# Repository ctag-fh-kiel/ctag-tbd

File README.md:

# dadamachines TBD-16

The first standalone desktop audio DSP platform based on [CTAG TBD](https://github.com/ctag-fh-kiel/ctag-tbd), with standard MIDI connectivity — designed to bring open-source audio processing beyond Eurorack.

**TBD-16** combines 50+ high-quality generators and effects in a modular, extensible architecture. It is built for musicians, educators, and audio researchers who want hands-on DSP without proprietary lock-in.

## Documentation

**[dadamachines.github.io/ctag-tbd](https://dadamachines.github.io/ctag-tbd/)**

## What This Fork Does

This repository is a fork of [ctag-fh-kiel/ctag-tbd](https://github.com/ctag-fh-kiel/ctag-tbd) (branch `p4_main`), adapted for the **dadamachines TBD-16** hardware. Our focus:

- **UI/UX** — Redesigned web interface with musician-friendly interaction patterns
- **Documentation** — Clear guides, example workflows, and UX guidelines for plugin developers
- **Desktop Hardware** — Standalone form factor with standard MIDI, no Eurorack required

The DSP engine, plugin system, and core firmware are developed upstream by [Robert Manzke / CTAG](https://www.creative-technologies.de/).

## Getting Started

See the [documentation](https://dadamachines.github.io/ctag-tbd/) for setup guides, plugin reference, and flashing instructions.

## Hardware Configurations

The firmware supports four hardware configurations for different board
variants — from a minimal flash-only build to the full TBD-16 with SD card
and RP2350 sequencer bridge. See [HARDWARE_CONFIGURATIONS.md](HARDWARE_CONFIGURATIONS.md) for
the feature matrix, build instructions, and Kconfig flag reference.

## Project Structure

```
components/         DSP plugins and sound processors
docs/               Sphinx documentation source
main/               Firmware entry point and system management
sdcard_image/       SD card image (samples, kits, presets, web UI)
simulator/          Desktop simulator for plugin development
tools/              Build scripts and sample utilities
generators/         Plugin scaffolding templates
```

### Building Documentation Locally

To build and preview the documentation (including the blog) on your local machine:

1.  **Install requirements**:
    ```bash
    pip install -r docs/requirements.txt
    ```

2.  **Build HTML**:
    ```bash
    sphinx-build -b html -c docs/config docs build/docs
    ```
    
3.  **View**:
    Open `build/docs/index.html` in your browser.

## Community & Support

- [dadamachines Forum](https://forum.dadamachines.com) -- Ask questions, share patches, and connect with other TBD users and developers.
- [GitHub Issues](https://github.com/dadamachines/ctag-tbd/issues) -- Bug reports and feature requests.

## Contributing

Contributions are welcome — see [CONTRIBUTING.md](CONTRIBUTING.md) for the
full guide covering the branch model, CI pipelines, build instructions,
and artifact naming conventions.

## Acknowledgements

**CTAG TBD** was created by [Robert Manzke](https://github.com/ctag-fh-kiel/ctag-tbd) at the [Creative Technologies Arbeitsgruppe](https://www.creative-technologies.de/), Kiel University of Applied Sciences. 

The TBD-16 adaptation is led by [dadamachines](https://dadamachines.com).

UX and instrument design contributions by [Benjamin Weiss / instrument-design](https://instrument-design.com/work/).

## Funding

This project is partially funded through the [NGI0 Commons Fund](https://nlnet.nl/commonsfund), established by [NLnet](https://nlnet.nl/) with financial support from the European Commission's [Next Generation Internet](https://ngi.eu/) programme, under grant agreement No [101135429](https://cordis.europa.eu/project/id/101135429).

Not all work on TBD / TBD-16 is covered by NLnet funding.

## License

This repository contains code under two open-source software licenses:

**Core DSP Engine** (upstream [ctag-fh-kiel/ctag-tbd](https://github.com/ctag-fh-kiel/ctag-tbd)) -- [GNU General Public License (GPL 3.0)](https://www.gnu.org/licenses/gpl-3.0.txt). The audio engine, sound processors, and platform core. Modifications must be released under the same terms.

**dadamachines Additions** (web UI, browser-based flasher, plugins, documentation, tools) -- [GNU Lesser General Public License (LGPL 3.0)](https://www.gnu.org/licenses/lgpl-3.0.txt). Individual developers can freely use and contribute without copyleft affecting their own unrelated code. Companies must share modifications back or obtain a [commercial license](https://dadamachines.com/contact/).

**TBD-Core & TBD-16 Hardware** -- The dadamachines TBD-16 (desktop instrument) and TBD-Core (core DSP board for custom products) hardware designs are proprietary.

**Planned Open-Hardware Core Design** -- An open-hardware core design based on the same ESP32-P4 + RP2350 platform is planned for future publication in KiCad as an open-source reference.

**Original CTAG Hardware** (V1/V2) -- [Creative Commons Attribution-NonCommercial-ShareAlike 4.0 International (CC BY-NC-SA 4.0)](https://creativecommons.org/licenses/by-nc-sa/4.0/).

Copyright (c) 2020-2026 Robert Manzke. All rights reserved. (CTAG TBD core)

Copyright (c) 2014-2026 Johannes Elias Lohbihler for dadamachines. (TBD-16 adaptation, UI/UX, and Documentation)

See [LICENSE](LICENSE) for full details including trademark and commercial use terms.

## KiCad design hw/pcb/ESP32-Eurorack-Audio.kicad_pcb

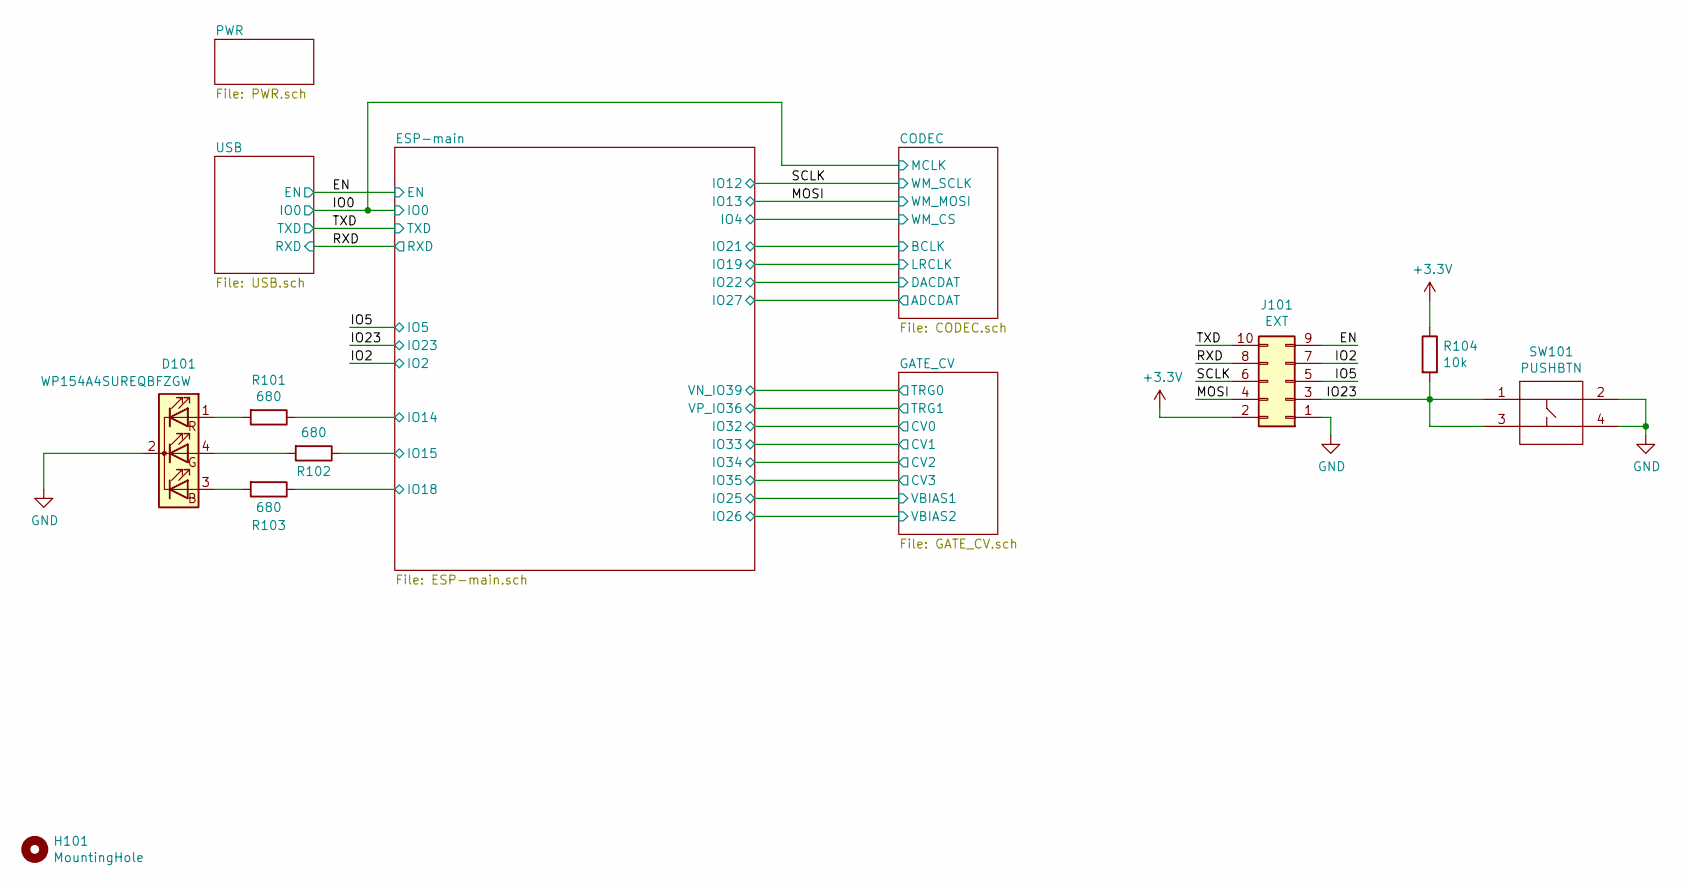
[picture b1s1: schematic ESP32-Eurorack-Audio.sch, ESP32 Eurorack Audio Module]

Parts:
D101: WP154A4SUREQBFZGW; LED_D5.0mm-4_RGB_Staggered_Pins
H101: MountingHole; MountingHole_2.7mm_M2.5_ISO7380
J101: EXT; PinHeader_2x05_P2.54mm_Vertical_SMD
R101, R102, R103: 680; R_0402_1005Metric
R104: 10k; R_0402_1005Metric
SW101: PUSHBTN; TactilePB_6x6

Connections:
+3V3: J101.2, R104.1; also elsewhere on the board
/EN: J101.9; also elsewhere on the board
/ESP-main/IO14: R101.1; also elsewhere on the board
/ESP-main/IO15: R102.1; also elsewhere on the board
/ESP-main/IO18: R103.1; also elsewhere on the board
/IO2: J101.7; also elsewhere on the board
/IO5: J101.5; also elsewhere on the board
/IO23: J101.3, R104.2, SW101.1, SW101.3; also elsewhere on the board
/MOSI: J101.4; also elsewhere on the board
/RXD: J101.8; also elsewhere on the board
/SCLK: J101.6; also elsewhere on the board
/TXD: J101.10; also elsewhere on the board
GND: D101.2 (K), J101.1, SW101.2, SW101.4; also elsewhere on the board
unnamed: D101.1 (RA), R101.2
unnamed: D101.3 (BA), R103.2
unnamed: D101.4 (GA), R102.2

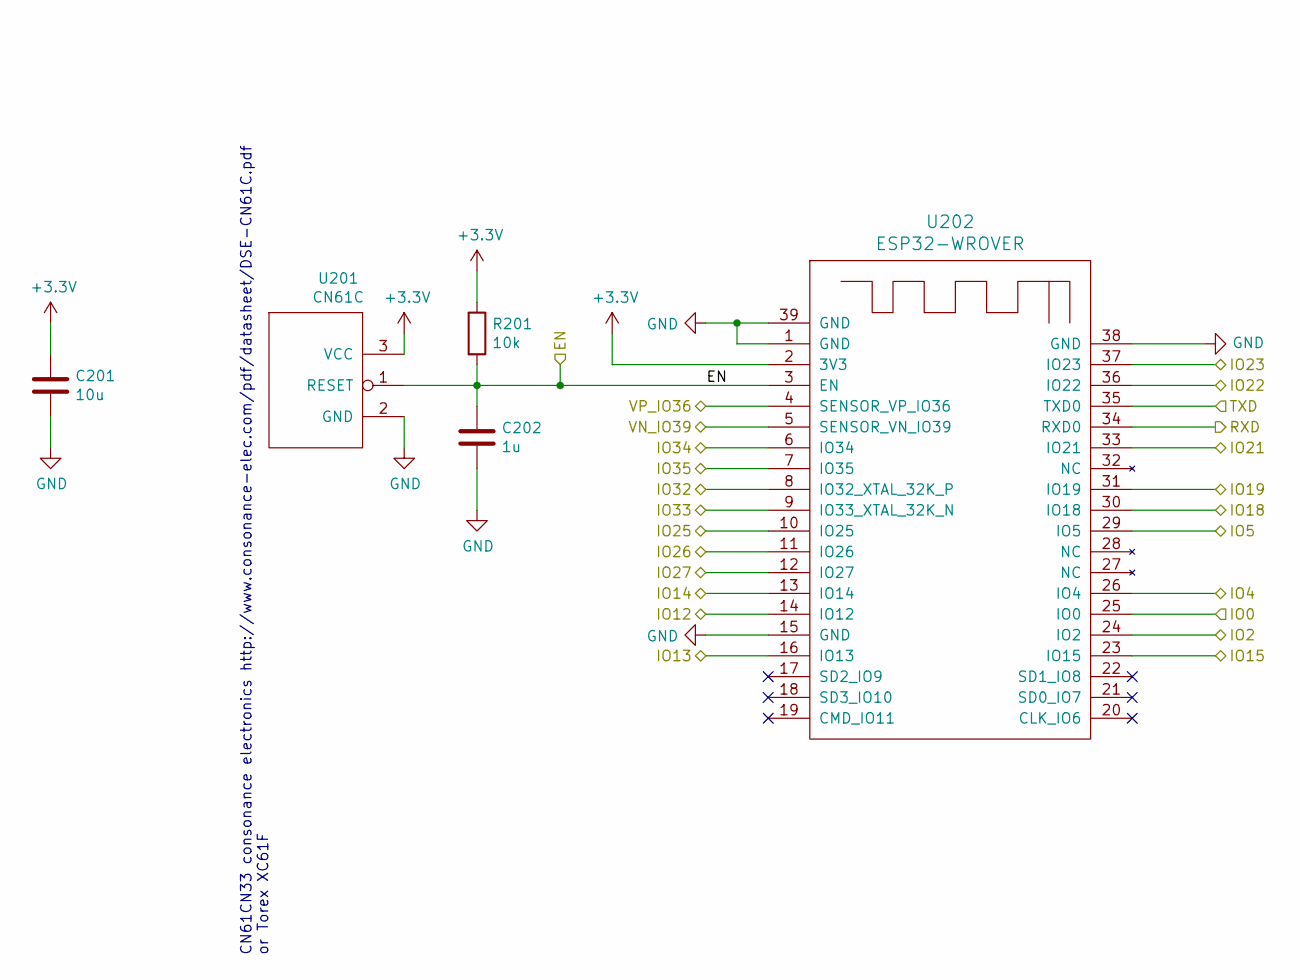
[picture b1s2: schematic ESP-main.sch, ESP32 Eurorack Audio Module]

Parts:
C201: 10u; C_0402_1005Metric
C202: 1u; C_0402_1005Metric
R201: 10k; R_0402_1005Metric
U201: CN61C; SOT-23
U202: ESP32-WROVER

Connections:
+3V3: C201.1, R201.1, U201.3 (VCC), U202.2 (3V3); also elsewhere on the board
/CODEC/ADCDAT: U202.12 (IO27); also elsewhere on the board
/CODEC/BCLK: U202.33 (IO21); also elsewhere on the board
/CODEC/DACDAT: U202.36 (IO22); also elsewhere on the board
/EN: C202.1, R201.2, U201.1 (RESET), U202.3 (EN); also elsewhere on the board
/ESP-main/IO4: U202.26 (IO4); also elsewhere on the board
/ESP-main/IO14: U202.13 (IO14); also elsewhere on the board
/ESP-main/IO15: U202.23 (IO15); also elsewhere on the board
/ESP-main/IO18: U202.30 (IO18); also elsewhere on the board
/ESP-main/IO19: U202.31 (IO19); also elsewhere on the board
/ESP-main/IO25: U202.10 (IO25); also elsewhere on the board
/ESP-main/IO26: U202.11 (IO26); also elsewhere on the board
/GATE_CV/CV0: U202.8 (IO32_XTAL_32K_P); also elsewhere on the board
/GATE_CV/CV1: U202.9 (IO33_XTAL_32K_N); also elsewhere on the board
/GATE_CV/CV2: U202.6 (IO34); also elsewhere on the board
/GATE_CV/CV3: U202.7 (IO35); also elsewhere on the board
/GATE_CV/TRG0: U202.5 (SENSOR_VN_IO39); also elsewhere on the board
/GATE_CV/TRG1: U202.4 (SENSOR_VP_IO36); also elsewhere on the board
/IO0: U202.25 (IO0); also elsewhere on the board
/IO2: U202.24 (IO2); also elsewhere on the board
/IO5: U202.29 (IO5); also elsewhere on the board
/IO23: U202.37 (IO23); also elsewhere on the board
/MOSI: U202.16 (IO13); also elsewhere on the board
/RXD: U202.34 (RXD0); also elsewhere on the board
/SCLK: U202.14 (IO12); also elsewhere on the board
/TXD: U202.35 (TXD0); also elsewhere on the board
GND: C201.2, C202.2, U201.2 (GND), U202.1 (GND), U202.15 (GND), U202.38 (GND), U202.39 (GND); also elsewhere on the board

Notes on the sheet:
CN61CN33 consonance electronics http://www.consonance-elec.com/pdf/datasheet/DSE-CN61C.pdf or Torex XC61F

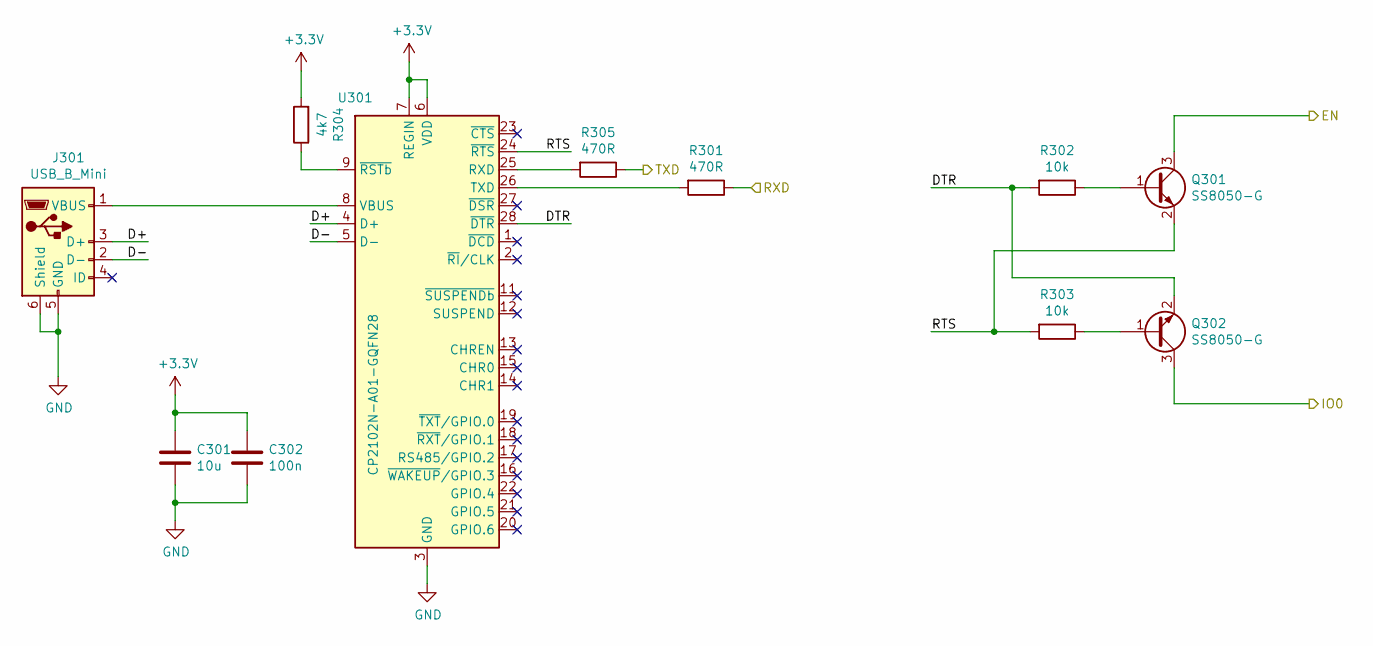
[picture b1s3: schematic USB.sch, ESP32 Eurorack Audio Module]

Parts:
C301: 10u; C_0402_1005Metric
C302: 100n; C_0402_1005Metric
J301: USB_B_Mini; USB_Mini-B_Tensility_54-00023_Vertical
Q301, Q302: SS8050-G; SOT-23
R301, R305: 470R; R_0402_1005Metric
R302, R303: 10k; R_0402_1005Metric
R304: 4k7; R_0402_1005Metric
U301: CP2102N-A01-GQFN28; QFN-28-1EP_5x5mm_P0.5mm_EP3.35x3.35mm

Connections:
+3V3: C301.1, C302.1, R304.2, U301.6 (VDD), U301.7 (REGIN); also elsewhere on the board
/EN: Q301.3 (C); also elsewhere on the board
/IO0: Q302.3 (C); also elsewhere on the board
/RXD: R301.1; also elsewhere on the board
/TXD: R305.1; also elsewhere on the board
/USB/D+: J301.3 (D+), U301.4 (D+)
/USB/D-: J301.2 (D-), U301.5 (D-)
/USB/DTR: Q302.2 (E), R302.2, U301.28 (~DTR)
/USB/RTS: Q301.2 (E), R303.2, U301.24 (~RTS)
GND: C301.2, C302.2, J301.5 (GND), J301.6 (Shield), U301.3 (GND), U301.29 (GND); also elsewhere on the board
unnamed: J301.1 (VBUS), U301.8 (VBUS)
unnamed: Q301.1 (B), R302.1
unnamed: Q302.1 (B), R303.1
unnamed: R301.2, U301.26 (TXD)
unnamed: R304.1, U301.9 (~RSTb)
unnamed: R305.2, U301.25 (RXD)

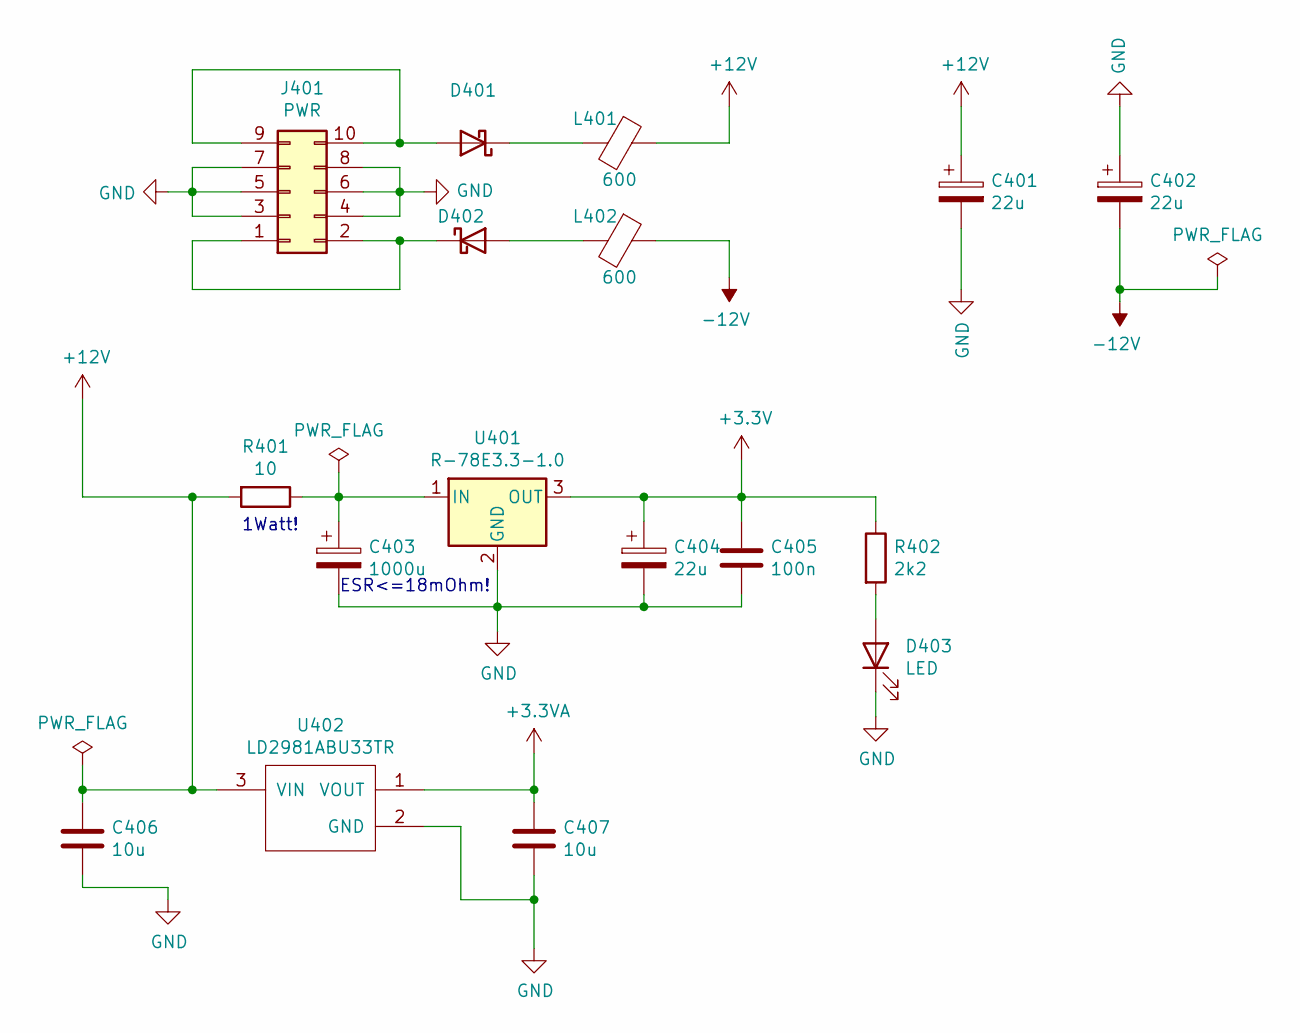
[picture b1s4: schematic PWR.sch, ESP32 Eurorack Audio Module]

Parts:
C401, C402, C404: 22u; C_0805_2012Metric
C403: 1000u; CP_Elec_10x12.6
C405: 100n; C_0402_1005Metric
C406: 10u; C_0805_2012Metric
C407: 10u; C_0402_1005Metric
D401, D402: D_SOD-123
D403: LED; LED_0805_2012Metric
J401: PWR; PinHeader_2x05_P2.54mm_Vertical
L401, L402: 600; C_0805_2012Metric
R401: 10; R_2512_6332Metric
R402: 2k2; R_0402_1005Metric
U401: R-78E3.3-1.0; SIP3_11.6x8.5mm
U402: LD2981ABU33TR; SOT-89-3

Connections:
+3.3VA: C407.1, U402.1 (VOUT); also elsewhere on the board
+3V3: C404.1, C405.1, R402.1, U401.3 (OUT); also elsewhere on the board
+12V: C401.1, C406.1, L401.1, R401.2, U402.3 (VIN); also elsewhere on the board
-12V: C402.2, L402.1; also elsewhere on the board
GND: C401.2, C402.1, C403.2, C404.2, C405.2, C406.2, C407.2, D403.1 (K), J401.3, J401.4, J401.5, J401.6, J401.7, J401.8, U401.2 (GND), U402.2 (GND); also elsewhere on the board
unnamed: C403.1, R401.1, U401.1 (IN)
unnamed: D401.1 (K), L401.2
unnamed: D401.2 (A), J401.9, J401.10
unnamed: D402.1 (K), J401.1, J401.2
unnamed: D402.2 (A), L402.2
unnamed: D403.2 (A), R402.2

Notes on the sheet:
ESR<=18mOhm!
1Watt!

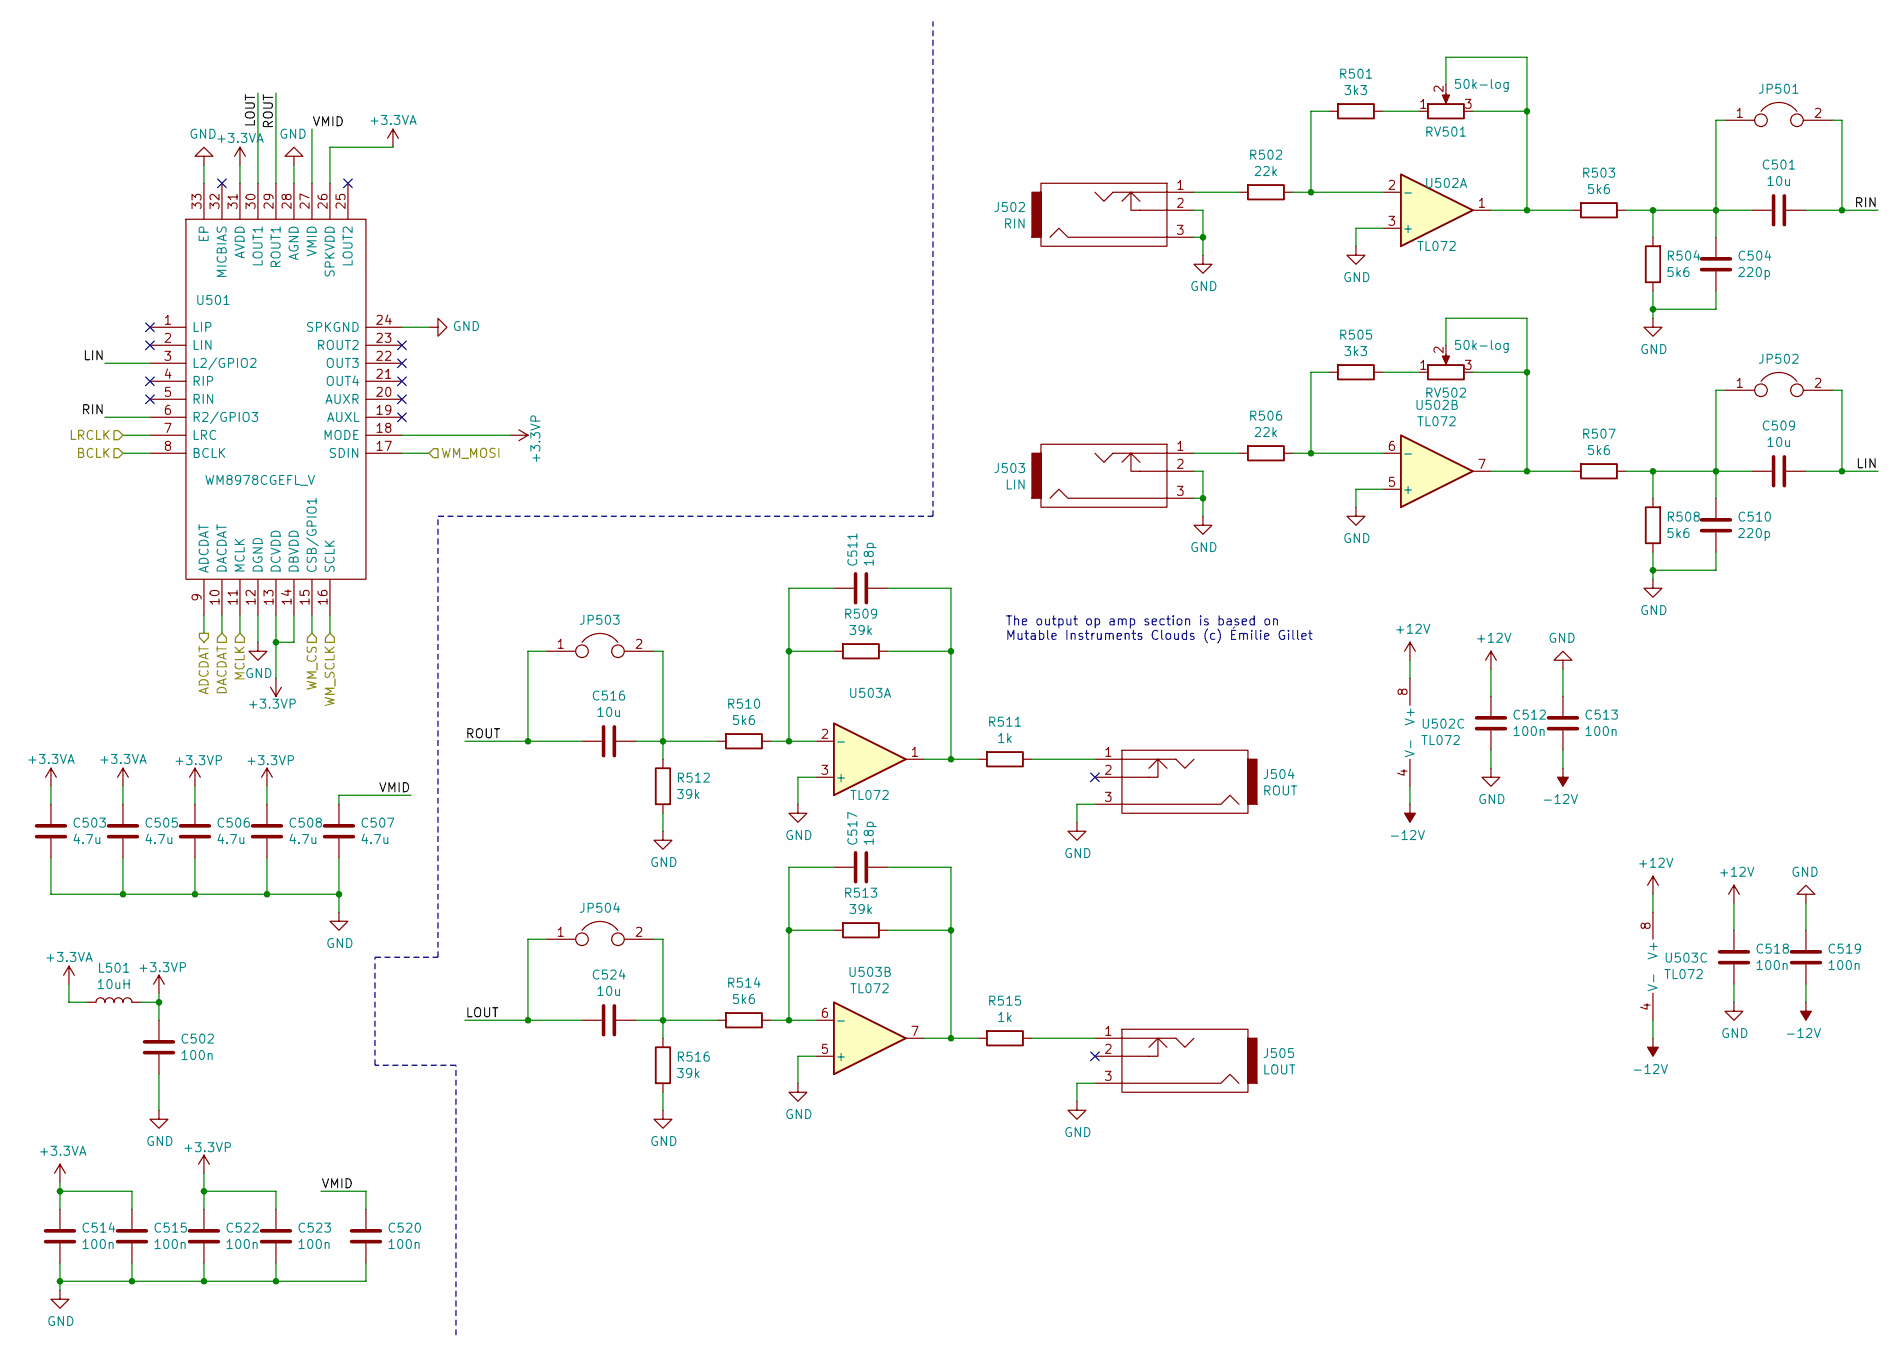
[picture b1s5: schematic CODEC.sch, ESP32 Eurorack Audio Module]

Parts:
C501, C509, C516, C524: 10u; C_0402_1005Metric
C502, C512, C513, C514, C515, C518, C519, C520, C522, C523: 100n; C_0402_1005Metric
C503, C505, C506, C507, C508: 4.7u; C_0402_1005Metric
C504, C510: 220p; C_0402_1005Metric
C511, C517: 18p; C_0402_1005Metric
J502: RIN; THONKICONN
J503: LIN; THONKICONN
J504: ROUT; THONKICONN
J505: LOUT; THONKICONN
JP501, JP502, JP503, JP504: SolderJumper-2_P1.3mm_Open_RoundedPad1.0x1.5mm
L501: 10uH; C_0603_1608Metric
R501, R505: 3k3; R_0402_1005Metric
R502, R506: 22k; R_0402_1005Metric
R503, R504, R507, R508, R510, R514: 5k6; R_0402_1005Metric
R509, R512, R513, R516: 39k; R_0402_1005Metric
R511, R515: 1k; R_0402_1005Metric
RV501, RV502: 50k-log; THONK-SONG-HUEI-R0904N-L-25-KQ_RED
U501: WM8978CGEFL_V; QFN-32-1EP_5x5mm_P0.5mm_EP3.65x3.65mm_ThermalVias; Mouser Part Number 238-WM8978CGEFL/V
U502, U503: TL072; SOIC-8_3.9x4.9mm_P1.27mm

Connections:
+3.3VA: C503.1, C505.1, C514.1, C515.1, L501.1, U501.26 (SPKVDD), U501.31 (AVDD); also elsewhere on the board
+3.3VP: C502.1, C506.1, C508.1, C522.1, C523.1, L501.2, U501.13 (DCVDD), U501.14 (DBVDD), U501.18 (MODE)
+12V: C512.1, C518.1, U502.8 (V+), U503.8 (V+); also elsewhere on the board
-12V: C513.2, C519.2, U502.4 (V-), U503.4 (V-); also elsewhere on the board
/CODEC/ADCDAT: U501.9 (ADCDAT); also elsewhere on the board
/CODEC/BCLK: U501.8 (BCLK); also elsewhere on the board
/CODEC/DACDAT: U501.10 (DACDAT); also elsewhere on the board
/CODEC/LIN: C509.1, JP502.2, U501.3 (L2/GPIO2)
/CODEC/LOUT: C524.2, JP504.1, U501.30 (LOUT1)
/CODEC/RIN: C501.1, JP501.2, U501.6 (R2/GPIO3)
/CODEC/ROUT: C516.2, JP503.1, U501.29 (ROUT1)
/CODEC/VMID: C507.1, C520.1, U501.27 (VMID)
/ESP-main/IO4: U501.15 (CSB/GPIO1); also elsewhere on the board
/ESP-main/IO19: U501.7 (LRC); also elsewhere on the board
/IO0: U501.11 (MCLK); also elsewhere on the board
/MOSI: U501.17 (SDIN); also elsewhere on the board
/SCLK: U501.16 (SCLK); also elsewhere on the board
GND: C502.2, C503.2, C504.2, C505.2, C506.2, C507.2, C508.2, C510.2, C512.2, C513.1, C514.2, C515.2, C518.2, C519.1, C520.2, C522.2, C523.2, J502.2, J502.3, J503.2, J503.3, J504.3, J505.3, R504.1, R508.1, R512.2, R516.2, U501.12 (DGND), U501.24 (SPKGND), U501.28 (AGND), U501.33 (EP), U502.3 (+), U502.5 (+), U503.3 (+), U503.5 (+); also elsewhere on the board
unnamed: C501.2, C504.1, JP501.1, R503.1, R504.2
unnamed: C509.2, C510.1, JP502.1, R507.1, R508.2
unnamed: C511.1, R509.2, R510.1, U503.2 (-)
unnamed: C511.2, R509.1, R511.2, U503.1
unnamed: C516.1, JP503.2, R510.2, R512.1
unnamed: C517.1, R513.2, R514.1, U503.6 (-)
unnamed: C517.2, R513.1, R515.2, U503.7
unnamed: C524.1, JP504.2, R514.2, R516.1
unnamed: J502.1, R502.2
unnamed: J503.1, R506.2
unnamed: J504.1, R511.1
unnamed: J505.1, R515.1
unnamed: R501.1, RV501.1
unnamed: R501.2, R502.1, U502.2 (-)
unnamed: R503.2, RV501.2, RV501.3, U502.1
unnamed: R505.1, RV502.1
unnamed: R505.2, R506.1, U502.6 (-)
unnamed: R507.2, RV502.2, RV502.3, U502.7

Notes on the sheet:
The output op amp section is based on Mutable Instruments Clouds (c) Émilie Gillet

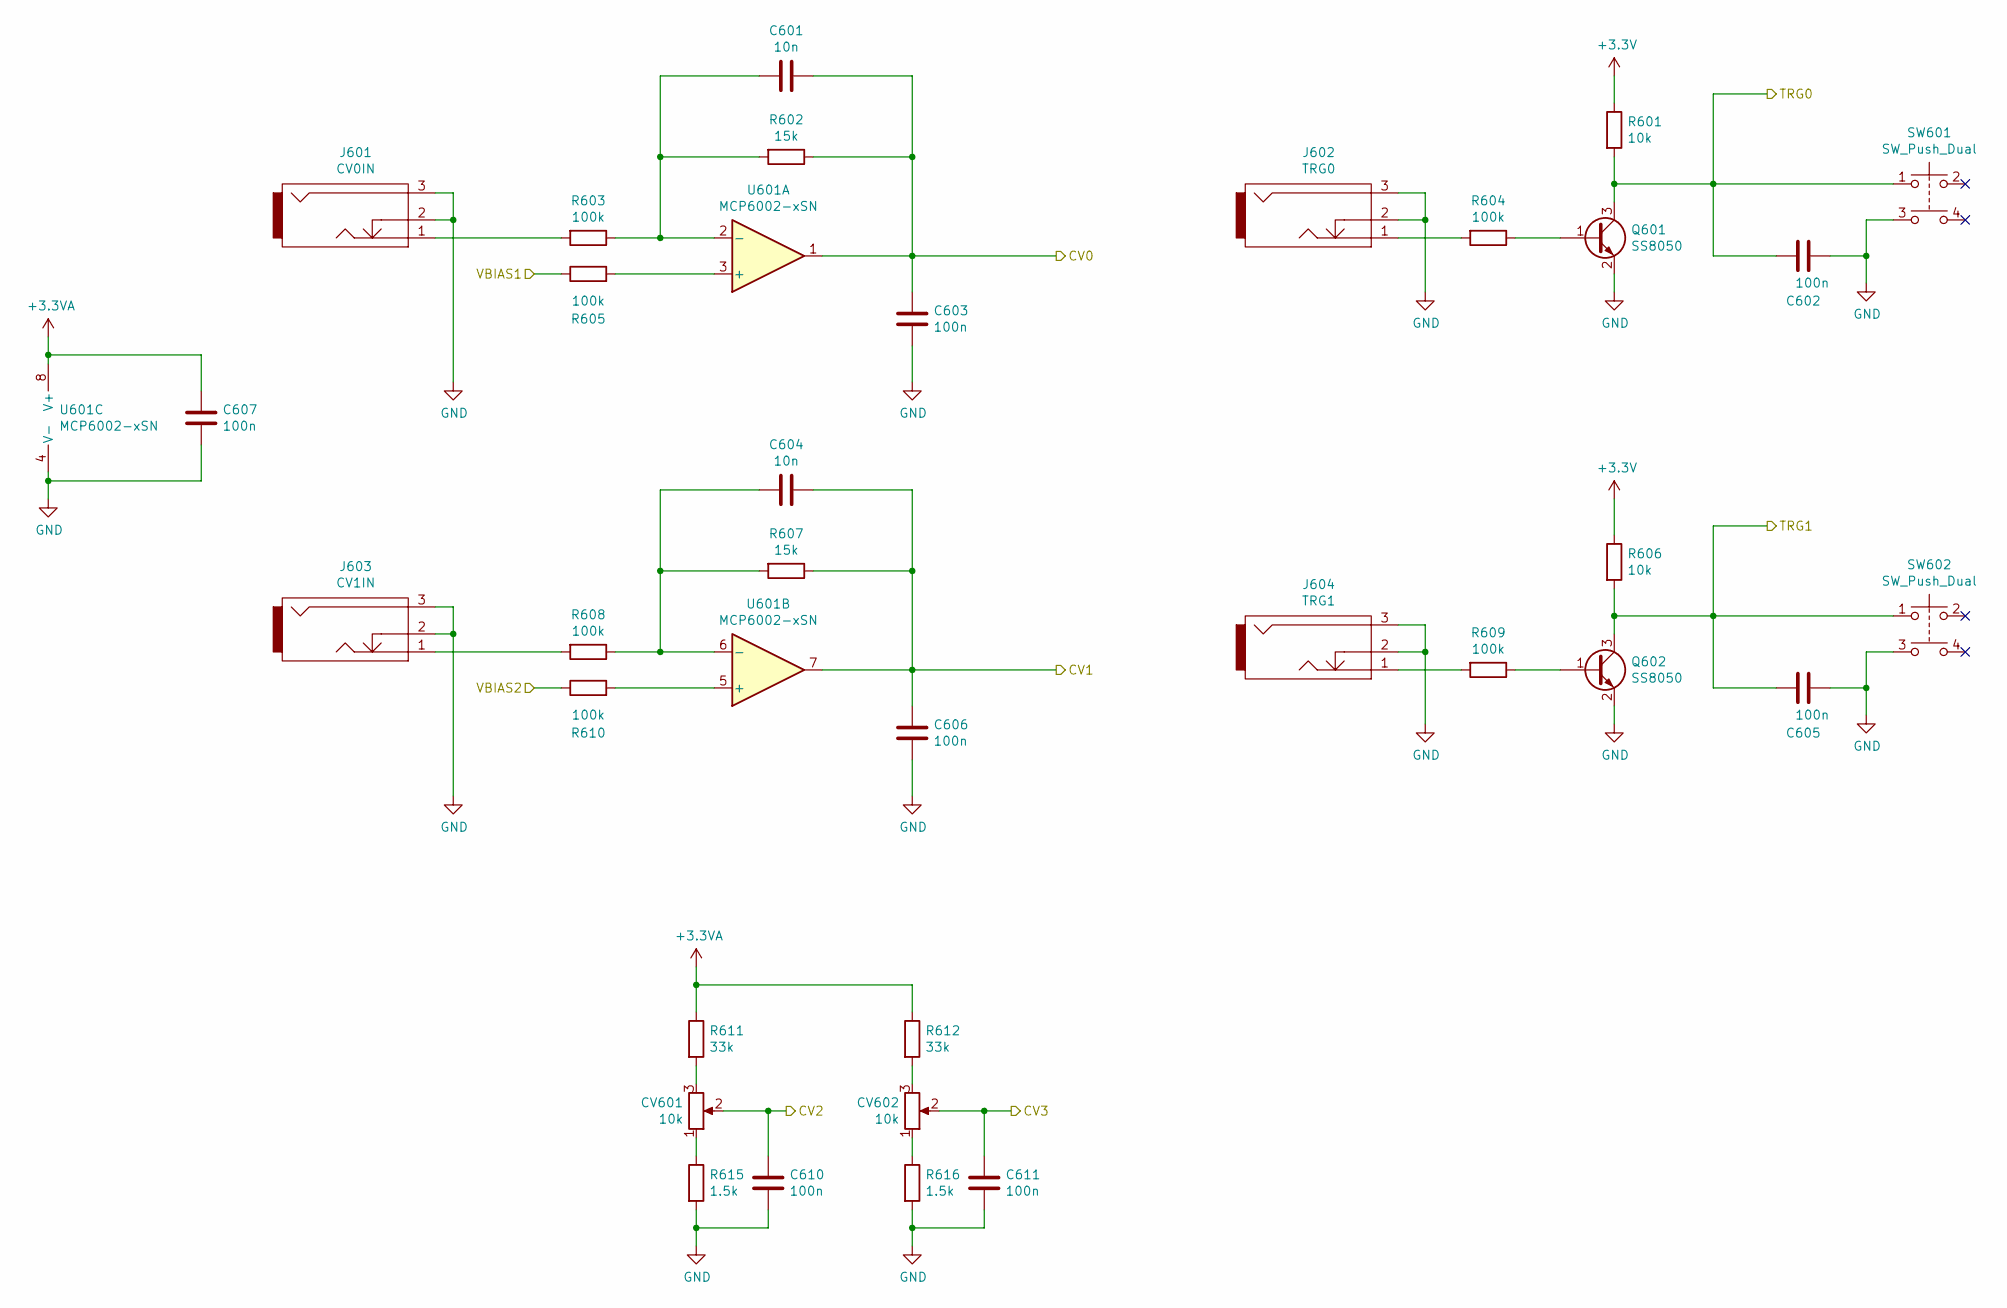
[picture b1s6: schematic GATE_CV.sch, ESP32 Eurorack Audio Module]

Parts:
C601, C604: 10n; C_0402_1005Metric
C602, C603, C605, C606, C607, C610, C611: 100n; C_0402_1005Metric
CV601, CV602: 10k; THONK-SONG-HUEI-R0904N-L-25-KQ_RED
J601: CV0IN; THONKICONN
J602: TRG0; THONKICONN
J603: CV1IN; THONKICONN
J604: TRG1; THONKICONN
Q601, Q602: SS8050; SOT-23
R601, R606: 10k; R_0402_1005Metric
R602, R607: 15k; R_0402_1005Metric
R603, R604, R605, R608, R609, R610: 100k; R_0402_1005Metric
R611, R612: 33k; R_0402_1005Metric
R615, R616: 1.5k; R_0402_1005Metric
SW601, SW602: SW_Push_Dual; 5GTH935
U601: MCP6002-xSN; SO-8_3.9x4.9mm_P1.27mm

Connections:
+3.3VA: C607.1, R611.1, R612.1, U601.8 (V+); also elsewhere on the board
+3V3: R601.1, R606.1; also elsewhere on the board
/ESP-main/IO25: R605.1; also elsewhere on the board
/ESP-main/IO26: R610.1; also elsewhere on the board
/GATE_CV/CV0: C601.1, C603.1, R602.1, U601.1; also elsewhere on the board
/GATE_CV/CV1: C604.1, C606.1, R607.1, U601.7; also elsewhere on the board
/GATE_CV/CV2: C610.2, CV601.2; also elsewhere on the board
/GATE_CV/CV3: C611.2, CV602.2; also elsewhere on the board
/GATE_CV/TRG0: C602.2, Q601.3 (C), R601.2, SW601.1; also elsewhere on the board
/GATE_CV/TRG1: C605.2, Q602.3 (C), R606.2, SW602.1; also elsewhere on the board
GND: C602.1, C603.2, C605.1, C606.2, C607.2, C610.1, C611.1, J601.2, J601.3, J602.2, J602.3, J603.2, J603.3, J604.2, J604.3, Q601.2 (E), Q602.2 (E), R615.2, R616.2, SW601.3, SW602.3, U601.4 (V-); also elsewhere on the board
unnamed: C601.2, R602.2, R603.1, U601.2 (-)
unnamed: C604.2, R607.2, R608.1, U601.6 (-)
unnamed: CV601.1, R615.1
unnamed: CV601.3, R611.2
unnamed: CV602.1, R616.1
unnamed: CV602.3, R612.2
unnamed: J601.1, R603.2
unnamed: J602.1, R604.2
unnamed: J603.1, R608.2
unnamed: J604.1, R609.2
unnamed: Q601.1 (B), R604.1
unnamed: Q602.1 (B), R609.1
unnamed: R605.2, U601.3 (+)
unnamed: R610.2, U601.5 (+)

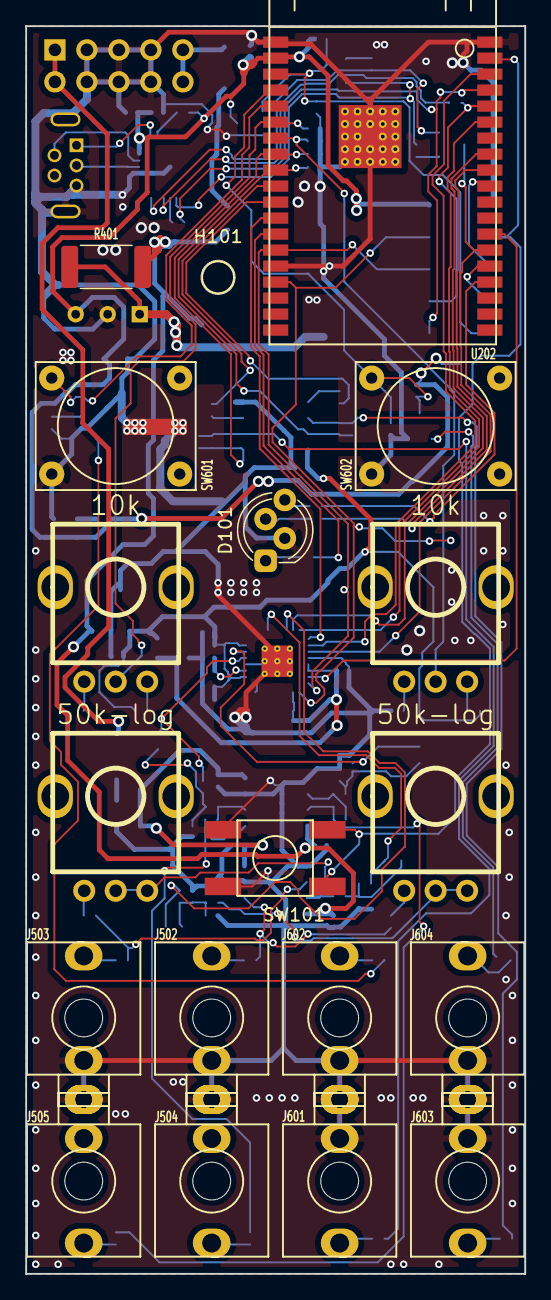
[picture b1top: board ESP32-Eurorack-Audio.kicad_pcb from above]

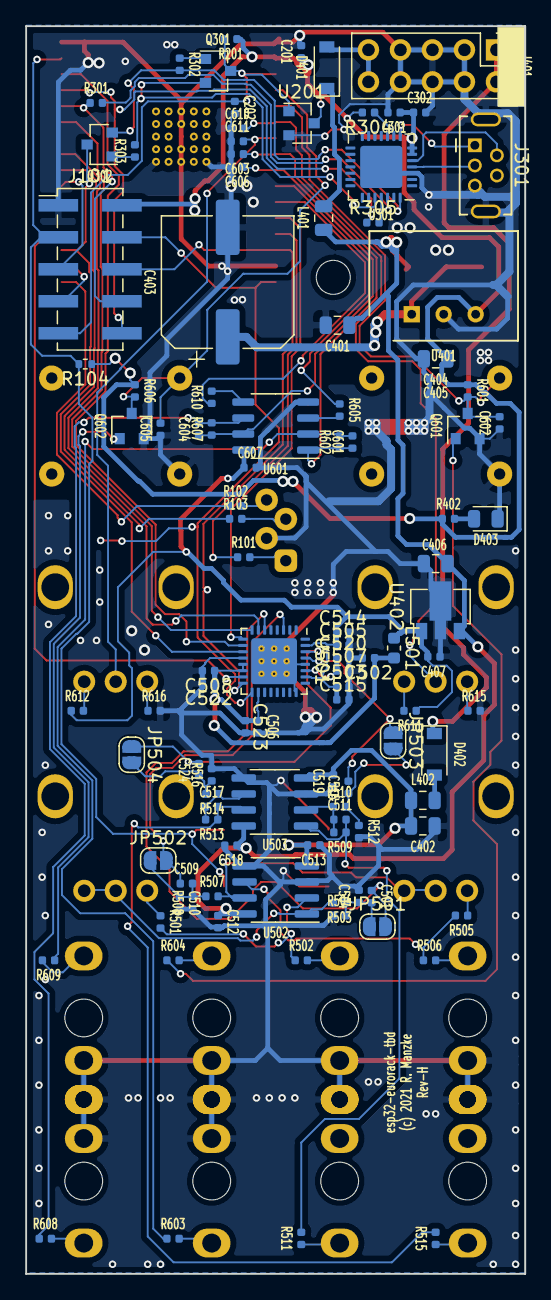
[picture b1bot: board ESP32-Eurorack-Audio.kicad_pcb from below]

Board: 2 copper layers, 39.6 x 99.1 mm, 128 parts (109 on the bottom side), 87 nets.

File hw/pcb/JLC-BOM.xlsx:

Comment | Designator | Footprint | LCSC |  |  |  |  | Quantity | Designation | Supplier and ref
WM8978CGEFL_V | U501 | QFN-32-1EP_5x5mm_P0.5mm_EP3.65x3.65mm_ThermalVias | C323850 |  |  |  |  | 2 | 10k
10uH | L501 | C_0603_1608Metric | C1035 |  |  |  |  | 1 | CP2102N-A01-GQFN28
100n | C523,C522,C520,C515,C514,C502,C611,C610,C607,C606,C605,C603,C602,C519,C518,C513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 | C_0402_1005Metric | C1525 |  |  |  |  | 1 | PWR
4.7u | C508,C507,C505,C503,C506 | C_0402_1005Metric | C23733 |  |  |  |  | 1 | EXT
Schottky Diode | D402,D401 | D_SOD-123 | C8598 |  |  |  |  | 1 | CAL
MCP6002-xSN | U601 | SO-8_3.9x4.9mm_P1.27mm | C7377 |  |  |  |  | 6 | 10k
TL072 | U503,U502 | SOIC-8_3.9x4.9mm_P1.27mm | C6961 |  |  |  |  | 1 | WM8978CGEFL_V
CP2102N-A01-GQFN28 | U301 | QFN-28-1EP_5x5mm_P0.5mm_EP3.35x3.35mm | C6568 |  |  |  |  | 1 | 10uH
1.5k | R616,R615 | R_0402_1005Metric | C25867 |  |  |  |  | 1 | RIN
33k | R612,R611 | R_0402_1005Metric | C25779 |  |  |  |  | 1 | LIN
100k | R610,R609,R608,R605,R604,R603 | R_0402_1005Metric | C25741 |  |  |  |  | 1 | LOUT
15k | R607,R602 | R_0402_1005Metric | C25756 |  |  |  |  | 1 | ROUT
10k | R104,R606,R601,R303,R302,R201 | R_0402_1005Metric | C25744 |  |  |  |  | 19 | 100n
39k | R516,R513,R512,R509 | R_0402_1005Metric | C25783 |  |  |  |  | 5 | 4.7u
1k | R515,R511 | R_0402_1005Metric | C11702 |  |  |  |  | 4 | ~
5k6 | R514,R510,R508,R507,R504,R503 | R_0402_1005Metric | C25908 |  |  |  |  | 1 | WP154A4SUREQBFZGW
22k | R506,R502 | R_0402_1005Metric | C25768 |  |  |  |  | 2 | 50k-log
3k3 | R505,R501 | R_0402_1005Metric | C25890 |  |  |  |  | 1 | R-78E3.3-1.0
2k2 | R402 | R_0402_1005Metric | C25879 |  |  |  |  | 1 | MountingHole
470R | R301,R305 | R_0402_1005Metric | C25117 |  |  |  |  | 2 | ~
4k7 | R304 | R_0402_1005Metric | C25900
680 | R103,R102,R101 | R_0402_1005Metric | C25130 |  |  |  |  | 1 | MIC803
SS8050 | Q602,Q601 | SOT-23 | C2150 |  |  |  |  | 1 | MCP6002-xSN
SS8050-G | Q302,Q301 | SOT-23 | C2150 |  |  |  |  | 2 | TL072
600 | L402,L401 | C_0805_2012Metric | C1017 |  |  |  |  | 1 | ADP7118
LED | D403 | LED_0805_2012Metric | C84256 |  |  |  |  | 1 | ESP32-WROVER
10n | C604,C601 | C_0402_1005Metric | C15195 |  |  |  |  | 2 | SW_Push_Dual
10u | C524,C516,C509,C501,C407,C301,C201 | C_0402_1005Metric | C15525 |  |  |  |  | 2 | 1.5k
18p | C517,C511 | C_0402_1005Metric | C1549 |  |  |  |  | 2 | 33k
220p | C510,C504 | C_0402_1005Metric | C1530 |  |  |  |  | 6 | 100k
10u | C406 | C_0805_2012Metric | C15850 |  |  |  |  | 2 | 15k
22u | C404,C402,C401 | C_0805_2012Metric | C45783 |  |  |  |  | 4 | 39k
1u | C202 | C_0402_1005Metric | C52923 |  |  |  |  | 2 | 1k
Mini USB B Vertical | J301 | MINI-USB-TH_C13453 | C13453 |  |  |  |  | 6 | 5k6
LD2981ABU33TR | U402 | SOT-89 | C221514 |  |  |  |  | 2 | 22k
CN61CN33 | U201 | SOT-23 | C84113 |  |  |  |  | 2 | 3k3
 |  |  |  |  |  |  |  | 1 | 2k2
 |  |  |  |  |  |  |  | 1 | 10
 |  |  |  |  |  |  |  | 1 | 470R
 |  |  |  |  |  |  |  | 3 | 680
 |  |  |  |  |  |  |  | 2 | SS8050
 |  |  |  |  |  |  |  | 2 | SS8050-G
 |  |  |  |  |  |  |  | 2 | 600
 |  |  |  |  |  |  |  | 1 | Jumper_2_Open
 |  |  |  |  |  |  |  | 1 | TRG1
 |  |  |  |  |  |  |  | 1 | CV1IN
 |  |  |  |  |  |  |  | 1 | TRG0
 |  |  |  |  |  |  |  | 1 | CV0IN
 |  |  |  |  |  |  |  | 1 | LOUT
 |  |  |  |  |  |  |  | 1 | ROUT
 |  |  |  |  |  |  |  | 1 | LIN
 |  |  |  |  |  |  |  | 1 | RIN
 |  |  |  |  |  |  |  | 1 | USB_B_Micro
 |  |  |  |  |  |  |  | 1 | LED
 |  |  |  |  |  |  |  | 2 | 10n
 |  |  |  |  |  |  |  | 7 | 10u
 |  |  |  |  |  |  |  | 2 | 18p
 |  |  |  |  |  |  |  | 2 | 220p
 |  |  |  |  |  |  |  | 1 | 10u
 |  |  |  |  |  |  |  | 3 | 22u
 |  |  |  |  |  |  |  | 1 | 1000u
 |  |  |  |  |  |  |  | 1 | 1u

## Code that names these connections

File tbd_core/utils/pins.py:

from typing import Any
import esphome.config_validation as cv
from esphome import pins


CONF_PINS = 'pins'
CONF_TYPE = 'type'

CONF_SPI = 'spi'
CONF_SPI_HOST = 'host'
CONF_SCLK_PIN = 'sclk'
CONF_MOSI_PIN = 'mosi'
CONF_MISO_PIN = 'miso'
CONF_CS_PIN = 'cs'

CONF_I2C = 'i2c'
CONF_SCL_PIN = 'scl'
CONF_SDA_PIN = 'sda'


CONF_I2S = 'i2s'
CONF_MCLK_PIN = 'mclk'
CONF_BCLK_PIN = 'bclk'
CONF_WS_PIN = 'ws'
CONF_DOUT_PIN = 'dout'
CONF_DIN_PIN = 'din'


# SPI device config pinout
SPIPinConfig = {
    cv.Required(CONF_SPI_HOST): cv.int_,
    # clock pin (SCLK)
    cv.Required(CONF_SCLK_PIN): pins.gpio_output_pin_schema,
    # data out pin (MOSI)
    cv.Required(CONF_MOSI_PIN): pins.gpio_output_pin_schema,
    # data in pin (MISO)
    cv.Required(CONF_MISO_PIN): pins.gpio_input_pin_schema,
    # chip select pin (CS/SS)
    cv.Required(CONF_CS_PIN): pins.gpio_output_pin_schema,
}


# I2C device config pinout
I2CPinConfig = {
    # clock pin (SCL)
    cv.Required(CONF_SCL_PIN): pins.gpio_output_pin_schema,
    # bidirectional data pin (SDA)
    cv.Required(CONF_SDA_PIN): pins.gpio_output_pin_schema,

}


# I2C audio data pinout
I2SPinConfig = {
    # master clock (MCLK)
    cv.Optional(CONF_MCLK_PIN): pins.gpio_output_pin_schema,
    # bit clock (BCLK)
    cv.Required(CONF_BCLK_PIN): pins.gpio_output_pin_schema,
    # word select /left-right clock (WS/LRCK)
    cv.Required(CONF_WS_PIN): pins.gpio_output_pin_schema,
    # data out / DAC data pin (DOUT/DACDAT)
    cv.Required(CONF_DOUT_PIN): pins.gpio_output_pin_schema,
    # data in  / ADC data pin (DIN/ADCDAT)
    cv.Required(CONF_DIN_PIN): pins.gpio_input_pin_schema,
}


def get_pin_label(key: str, config: dict[str, Any]) -> str:
    return f'GPIO_NUM_{config[key]['number']}'


def get_spi_pinout_defines(prefix: str, config: dict[str, Any]) -> list[tuple[str, str]]:
    defines = [
        (f'{prefix}_HOST', f'SPI{config[CONF_SPI_HOST]}_HOST'),
        (f'{prefix}_PIN_SCLK', get_pin_label(CONF_SCLK_PIN, config)),
        (f'{prefix}_PIN_MOSI', get_pin_label(CONF_MOSI_PIN, config)),
        (f'{prefix}_PIN_MISO', get_pin_label(CONF_MISO_PIN, config)),
    ]
    if CONF_SCLK_PIN in config:
        defines.append((f'{prefix}_PIN_CS', get_pin_label(CONF_CS_PIN, config))),
    return defines


def get_i2c_pinout_defines(prefix: str, config: dict[str, Any]) -> list[tuple[str, str]]:
    return [
        (f'{prefix}_PIN_SCL', get_pin_label(CONF_SCL_PIN, config)),
        (f'{prefix}_PIN_SDA', get_pin_label(CONF_SDA_PIN, config)),
    ]


def get_i2s_pinout_defines(prefix: str, config: dict[str, Any]) -> list[tuple[str, str]]:
    defines = [
        (f'{prefix}_PIN_BCLK', get_pin_label(CONF_BCLK_PIN, config)),
        (f'{prefix}_PIN_WS', get_pin_label(CONF_WS_PIN, config)),
        (f'{prefix}_PIN_DOUT', get_pin_label(CONF_DOUT_PIN, config)),
        (f'{prefix}_PIN_DIN', get_pin_label(CONF_DIN_PIN, config)),
    ]
    if CONF_MCLK_PIN in config:
        defines.append((f'{prefix}_PIN_MCLK', get_pin_label(CONF_MCLK_PIN, config)))
    return defines


__all__ = [
    'SPIPinConfig',
    'I2CPinConfig',
    'I2SPinConfig',
    'CONF_PINS',
    'CONF_TYPE',
    'CONF_SPI',
    'CONF_SCLK_PIN',
    'CONF_MOSI_PIN',
    'CONF_MISO_PIN',
    'CONF_CS_PIN',
    'CONF_I2C',
    'CONF_SCL_PIN',
    'CONF_SDA_PIN',
    'CONF_I2S',
    'CONF_MCLK_PIN',
    'CONF_BCLK_PIN',
    'CONF_WS_PIN',
    'CONF_DOUT_PIN',
    'CONF_DIN_PIN',
    'get_spi_pinout_defines',
    'get_i2c_pinout_defines',
    'get_i2s_pinout_defines',
]

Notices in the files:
hw/pcb/CODEC.sch:
Licensed under CC BY-NC-SA 4.0
hw/pcb/ESP32-Eurorack-Audio.kicad_pcb:
(c) 2021 R. Manzke
